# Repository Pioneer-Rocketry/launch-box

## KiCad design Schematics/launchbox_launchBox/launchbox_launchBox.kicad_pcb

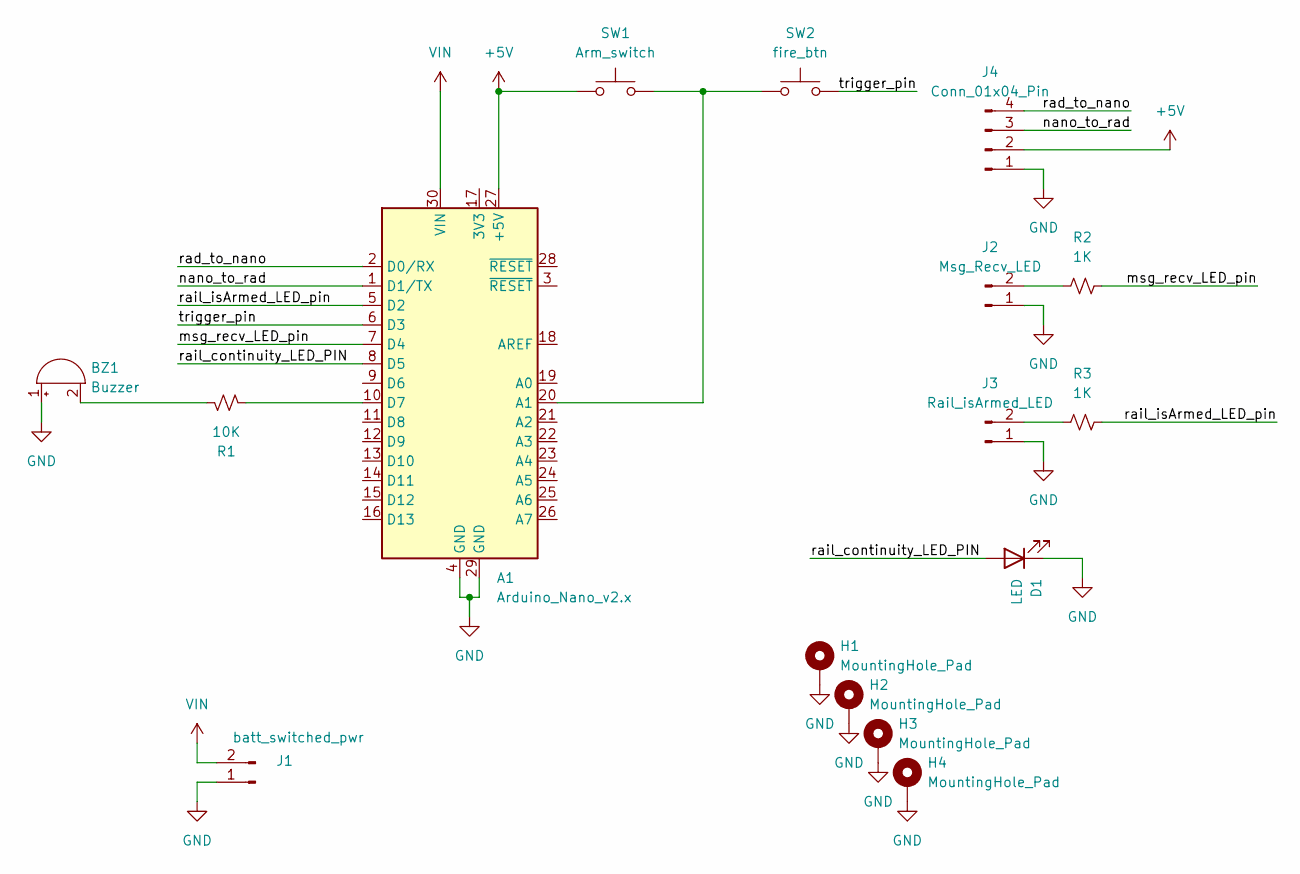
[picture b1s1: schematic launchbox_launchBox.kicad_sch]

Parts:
A1: Arduino_Nano_v2.x; Arduino_Nano
BZ1: Buzzer; PinHeader_1x02_P2.54mm_Vertical
D1: LED; PinHeader_1x02_P2.54mm_Vertical
H1, H2, H3, H4: MountingHole_Pad; MountingHole_3.2mm_M3_Pad_TopBottom
J1: batt_switched_pwr; PinHeader_1x02_P2.54mm_Vertical
J2: Msg_Recv_LED; PinHeader_1x02_P2.54mm_Vertical
J3: Rail_isArmed_LED; PinHeader_1x02_P2.54mm_Vertical
J4: Conn_01x04_Pin; PinHeader_1x04_P2.54mm_Vertical
R1: 10K; R_0603_1608Metric_Pad0.98x0.95mm_HandSolder
R2, R3: 1K; R_0603_1608Metric_Pad0.98x0.95mm_HandSolder
SW1: Arm_switch; PinHeader_1x02_P2.54mm_Vertical
SW2: fire_btn; PinHeader_1x02_P2.54mm_Vertical

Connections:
+5V: A1.27 (+5V), J4.2 (Pin_3), SW1.1 (A)
/msg_recv_LED_pin: A1.7 (D4), R2.2
/nano_to_rad: A1.1 (D1/TX), J4.3 (Pin_2)
/rad_to_nano: A1.2 (D0/RX), J4.4 (Pin_1)
/rail_continuity_LED_PIN: A1.8 (D5), D1.2 (A)
/rail_isArmed_LED_pin: A1.5 (D2), R3.2
/trigger_pin: A1.6 (D3), SW2.2
GND: A1.4 (GND), A1.29 (GND), BZ1.1 (-), D1.1 (K), H1.1, H2.1, H3.1, H4.1, J1.1, J2.1 (Pin_2), J3.1 (Pin_2), J4.1 (Pin_4)
unnamed: A1.20 (A1), SW1.2 (B), SW2.1
unnamed: A1.10 (D7), R1.2
unnamed: BZ1.2 (+), R1.1
unnamed: J2.2 (Pin_1), R2.1
unnamed: J3.2 (Pin_1), R3.1
VIN: A1.30 (VIN), J1.2

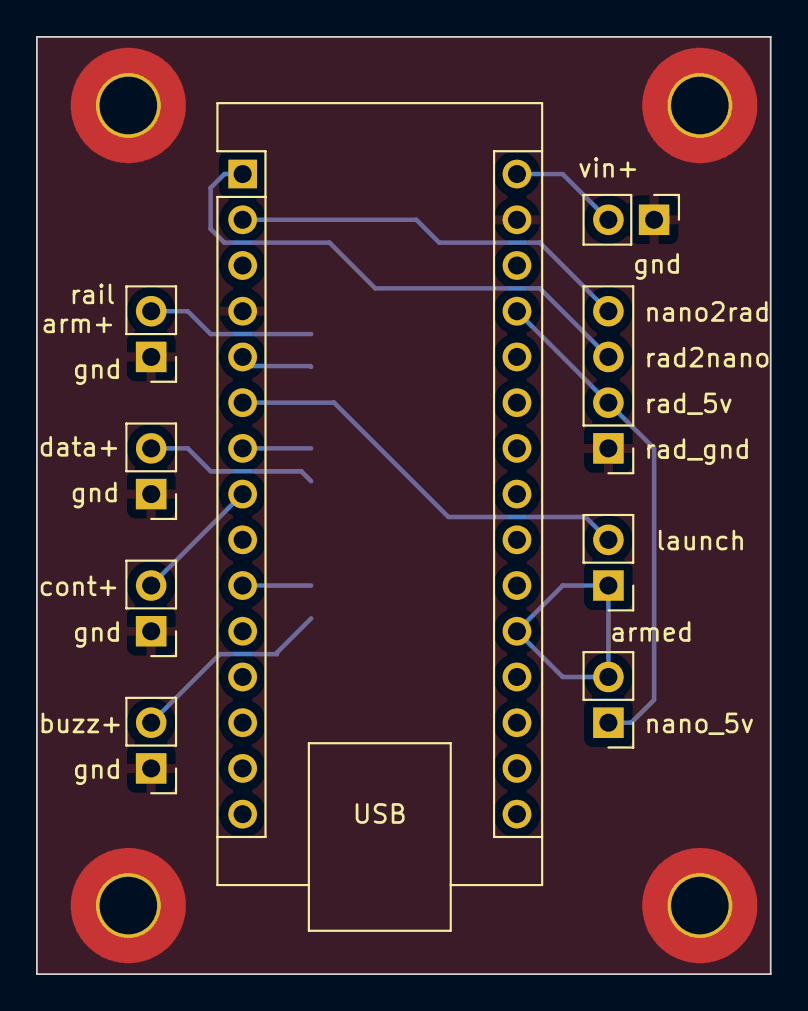
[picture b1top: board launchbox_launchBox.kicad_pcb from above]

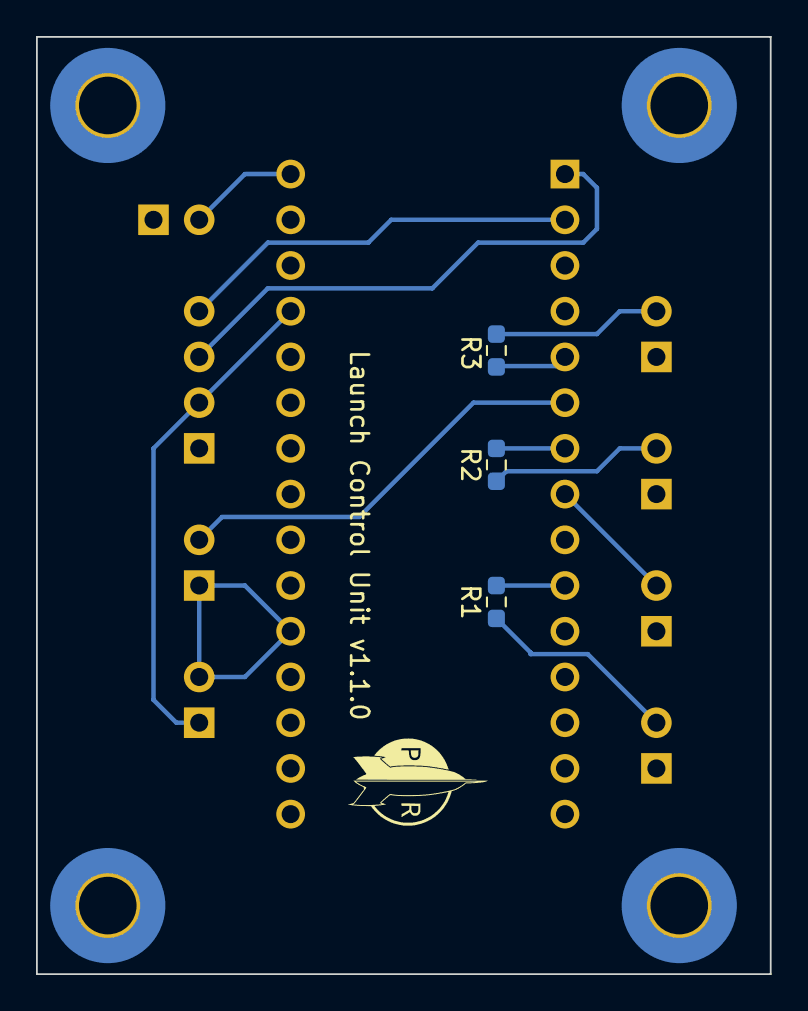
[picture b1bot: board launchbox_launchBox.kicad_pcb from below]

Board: 2 copper layers, 40.8 x 52.1 mm, 16 parts (3 on the bottom side), 14 nets.

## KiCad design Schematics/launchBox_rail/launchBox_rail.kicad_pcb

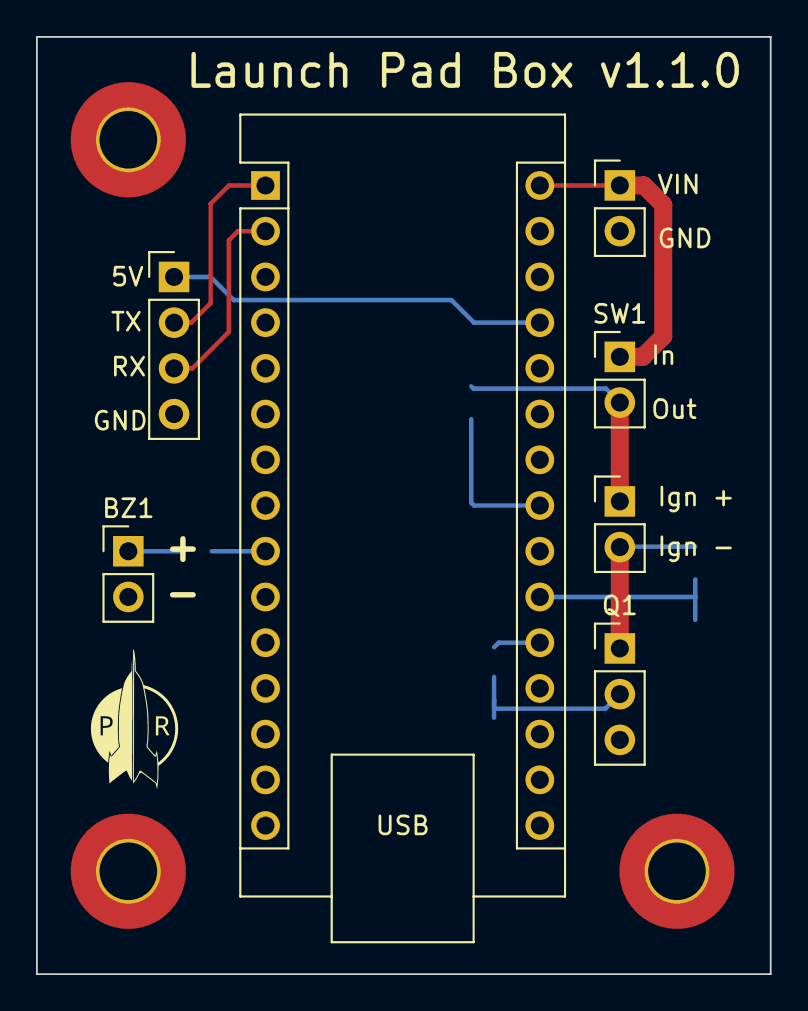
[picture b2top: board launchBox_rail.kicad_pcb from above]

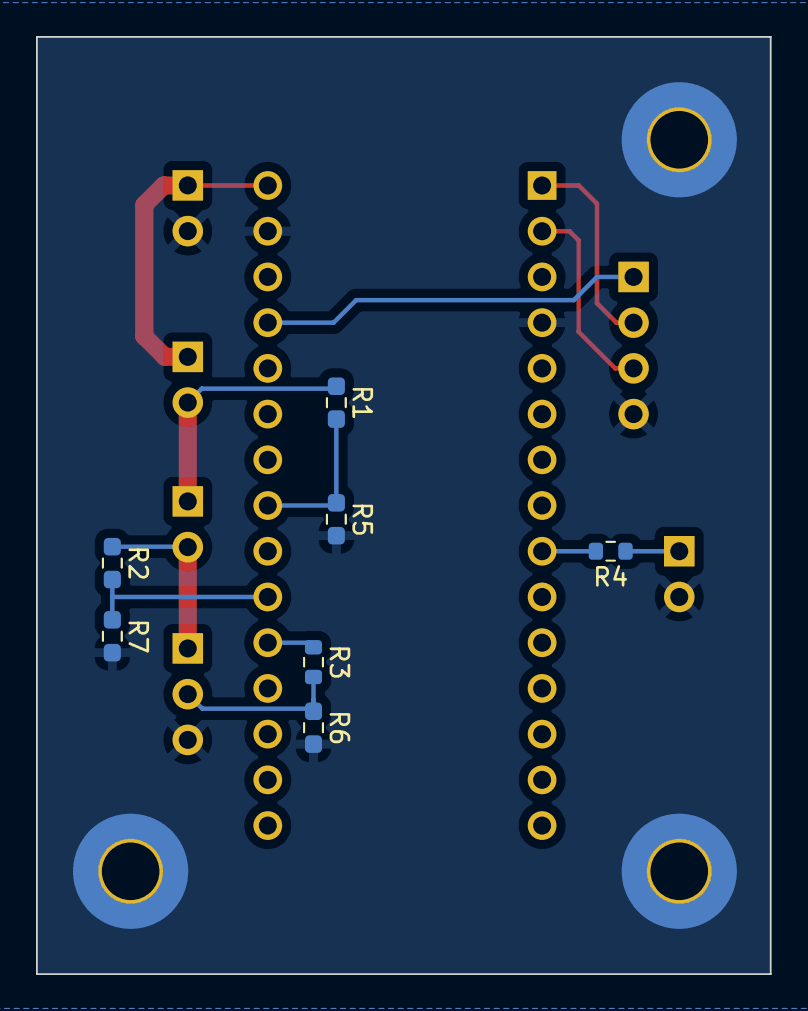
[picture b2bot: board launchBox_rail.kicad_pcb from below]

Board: 2 copper layers, 40.8 x 52.1 mm, 17 parts (7 on the bottom side), 13 nets.

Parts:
A1: Arduino_Nano_v3.x; Arduino_Nano
BZ1: Buzzer; PinHeader_1x02_P2.54mm_Vertical
H1, H2, H3: MountingHole_Pad; MountingHole_3.2mm_M3_Pad_TopBottom
J1, J3: Screw_Terminal_01x02; PinHeader_1x02_P2.54mm_Vertical
J2: Conn_01x04_Pin; PinHeader_1x04_P2.54mm_Vertical
Q1: NMOS; PinHeader_1x03_P2.54mm_Vertical
R1, R2: 7.5k; R_0603_1608Metric_Pad0.98x0.95mm_HandSolder
R3: 500; R_0603_1608Metric
R4: 10k; R_0603_1608Metric
R5, R7: 3k; R_0603_1608Metric_Pad0.98x0.95mm_HandSolder
R6: 10k; R_0603_1608Metric_Pad0.98x0.95mm_HandSolder
SW1: SW_MEC_5G; PinHeader_1x02_P2.54mm_Vertical

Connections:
+5V: A1.27 (+5V), J2.1
/armed: A1.23 (A4), R1.2, R5.1
/continuity: A1.21 (A2), R2.2, R7.1
/pyro_power: J3.1, R1.1, SW1.2 (B)
/radioRx: A1.2 (D0/RX), J2.3
/radioTx: A1.1 (D1/TX), J2.2
/trigger: A1.20 (A1), R3.1
GND: A1.4 (GND), A1.29 (GND), BZ1.2 (+), H1.1, H2.1, H3.1, J1.2, J2.4, Q1.3 (S), R5.2, R6.2, R7.2
unnamed: A1.9 (D6), R4.2
unnamed: BZ1.1 (-), R4.1
unnamed: J3.2, Q1.1 (D), R2.1
unnamed: Q1.2 (G), R3.2, R6.1
VIN: A1.30 (VIN), J1.1, SW1.1 (A)

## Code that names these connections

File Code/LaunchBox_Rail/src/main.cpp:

#include <Arduino.h>
#include <ArduinoJson.h>

const int ARMED_PIN             = A4;   // Voltage across the battery. Step down by 75%
const int IGN_CONTINUITY_PIN    = A7;   // Continuity across the igniter 

const int TRIGGER_PIN           = 2;    // Trigger pin (D2) for lighting the igniter
const int BUZZER_PIN            = 7;    // Buzzer pin (D7)
const int MANUAL_TRIG_GND      = 10;   // Override switch
const int MANUAL_TRIG_POS      = 11;
const int MANUAL_OVERRIDE_TOGGLE = 12;

const int TRIGGER_LENGTH        = 1000; // 1000 ms = 1 s

const float IS_ARMED_SET_POINT  = 3.4;  // Voltage at which the system is armed
const float HAS_CONTINUITY_POINT = 3.4; // Voltage at which the igniter has continuity
const float MANUAL_TRIG_POINT = 3.4;

const String pc_TOPIC           = "TOPIC";
const String pc_REQ_TRI         = "REQ_TRI";
const String pc_REQ_CON         = "REQ_CON";
const String pc_RES_CON         = "RES_CON";
const String pc_RES_TRI         = "RES_TRI";

const bool pc_debug                = false;


void startBuzzer()
{
  digitalWrite(BUZZER_PIN, HIGH);
}

void endBuzzer()
{
  digitalWrite(BUZZER_PIN, LOW);
}

void trigger()
{
  digitalWrite(TRIGGER_PIN, HIGH);
  delay(TRIGGER_LENGTH);
  digitalWrite(TRIGGER_PIN, LOW);
}

bool isArmedFunc()
{
  bool isArmed = false;

  int rawVoltage = analogRead(ARMED_PIN);
  
  float currentVoltage = rawVoltage * (5.0 / 1023.0); // clamps the voltage between 0V - 5V

  if (pc_debug)
  {
    // Serial.println("rawVoltage: " + String(rawVoltage));
    // Serial.println("currentVoltage: " + String(currentVoltage));
  }

  if (currentVoltage >= IS_ARMED_SET_POINT)
  {
    isArmed = true;
  }
  else
  {
    isArmed = false;
  }

  return isArmed;

}

bool hasContinuityFunc()
{
  bool hasContinuity = false;
  int rawValue = analogRead(IGN_CONTINUITY_PIN);
  float currentVoltage = rawValue * (5.0 / 1023.0); // clamps the voltage between 0V - 5V

  if (currentVoltage >= HAS_CONTINUITY_POINT)
  {
    hasContinuity = true;
  }
  else
  {
    hasContinuity = false;
  }

  return hasContinuity;
}

bool shouldManualTrigger()
{

  bool manualTrig = false;

  bool GND = digitalRead(MANUAL_TRIG_GND);
  bool POS = digitalRead(MANUAL_TRIG_POS);

  if (!GND && POS)
  {
    manualTrig = true;
    return manualTrig;
  }

  return manualTrig;

}

void setup() {
  // put your setup code here, to run once:
  pinMode(ARMED_PIN, INPUT);
  pinMode(IGN_CONTINUITY_PIN, INPUT);

  pinMode(MANUAL_TRIG_GND, INPUT_PULLUP);
  pinMode(MANUAL_TRIG_POS, INPUT);
  digitalWrite(MANUAL_TRIG_POS, LOW);
  
  pinMode(TRIGGER_PIN, OUTPUT);
  pinMode(BUZZER_PIN, OUTPUT);

  Serial.begin(19200);

}

void loop() {
  
  bool isArmed = false;
  bool hasContinuity = false;
  bool manualTrigger = false;
  String msg = "";
  JsonDocument doc;

  while (1)
  {
    isArmed = isArmedFunc();
    hasContinuity = hasContinuityFunc();
    manualTrigger = shouldManualTrigger();

    if (hasContinuity)
    {
      startBuzzer();
    }
    else
    {
      endBuzzer();
    }

    if (Serial.available())
    {
      if (pc_debug)
      {
        Serial.println("Serial.available()");
      }
      msg = Serial.readStringUntil('\n');
      msg.trim();
      if(msg.length() > 0)
      {
        const char* msgCStr = msg.c_str();
        if (pc_debug)
        {
          Serial.println("Msg length: " + String(msg.length()));
          Serial.println("msg: " + msg);
        }
        DeserializationError err1 = deserializeJson(doc, msgCStr);
        String err1Str = err1.f_str();
        if (err1 && pc_debug)
        {
          Serial.println("{\"TOPIC\":\"ERROR\",\"msg\":\"1. Error occured desearializing incoming msg:'"+err1Str+"'\",\"msgRecv\":\""+msg+"\"}");
        }
        else
        {
          String topic = doc[pc_TOPIC];

          if (topic == pc_REQ_TRI)
          {
            if (isArmed && hasContinuity)
            {
              trigger();
              doc.clear();
              String res = "{\"TOPIC\":\""+pc_RES_TRI+"\",\"msg\":\"success\"}";
              DeserializationError err2 = deserializeJson(doc, res.c_str());
              String err2Str = err2.f_str();
              if (err2 && pc_debug)
              {
                Serial.println("{\"TOPIC\":\"ERROR\",\"msg\":\"2. Error occured desearializing incoming msg:'"+err2Str+"'\"");
              }
              else
              {
                String resSerialize = "";
                serializeJson(doc, resSerialize); 
                Serial.println(resSerialize);
              }
            }
          }
          else if (topic == pc_REQ_CON)
          {
            doc.clear();
            String isArmedStr = String((int)isArmed);
            String hasContinuityStr = String((int)hasContinuity);

            String res = "{\"TOPIC\":\""+pc_RES_CON+"\",\"isArmed\":"+isArmedStr+",\"hasContinuity\":"+hasContinuity+"}";
            DeserializationError err2 = deserializeJson(doc, res.c_str());

            String err2Str = err2.f_str();
            if (err2 && pc_debug)
            {
              Serial.println("{\"TOPIC\":\"ERROR\",\"msg\":\"3. Error occured desearializing incoming msg:'"+err2Str+"'\"");
            }
            else
            {
              String resSerialize = "";
              serializeJson(doc, resSerialize);
              Serial.println(resSerialize);
            }
          }
        }
      }

    }
    else if (digitalRead(MANUAL_OVERRIDE_TOGGLE))
    {
      if (manualTrigger) // comes from launch control unit
      {
        if (isArmed && hasContinuity) // comes from launch pad box
        {
          trigger();
        }
      }
    }
  }
  
}

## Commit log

2024-09-17 Howdy
2024-12-11 removed
2025-10-24 Add files via upload
    Everything is done :)
2025-10-24 Add files via upload
    EVERYTHING IS DONE
2025-10-24 Deleted duplicate files
2025-10-24 Updated flow diagrams
2025-10-26 System block diagram
2025-11-05 Updating Handheld PCB
2025-11-05 completed launch box pcb
2025-11-06 Added wired override
2025-11-06 Added connection retrys
2025-11-06 Updated component layouts for LPB
2025-11-07 Updated PCB for LPB 80% done
2025-11-07 v1 of PCB for LPB is complete
2025-11-07 Finished LPB PCB design
2025-11-07 Fixed short
2025-11-07 Cleaned up rail side launch box schematic and PCB
2025-11-07 Clean it up a bit more
2025-11-07 Removed some of the of the component designators from the silkscreen
2025-11-07 Cleaned up handheld box schematic and fixed 3d model
2025-11-07 Added version, title, and PR logo to LCU
